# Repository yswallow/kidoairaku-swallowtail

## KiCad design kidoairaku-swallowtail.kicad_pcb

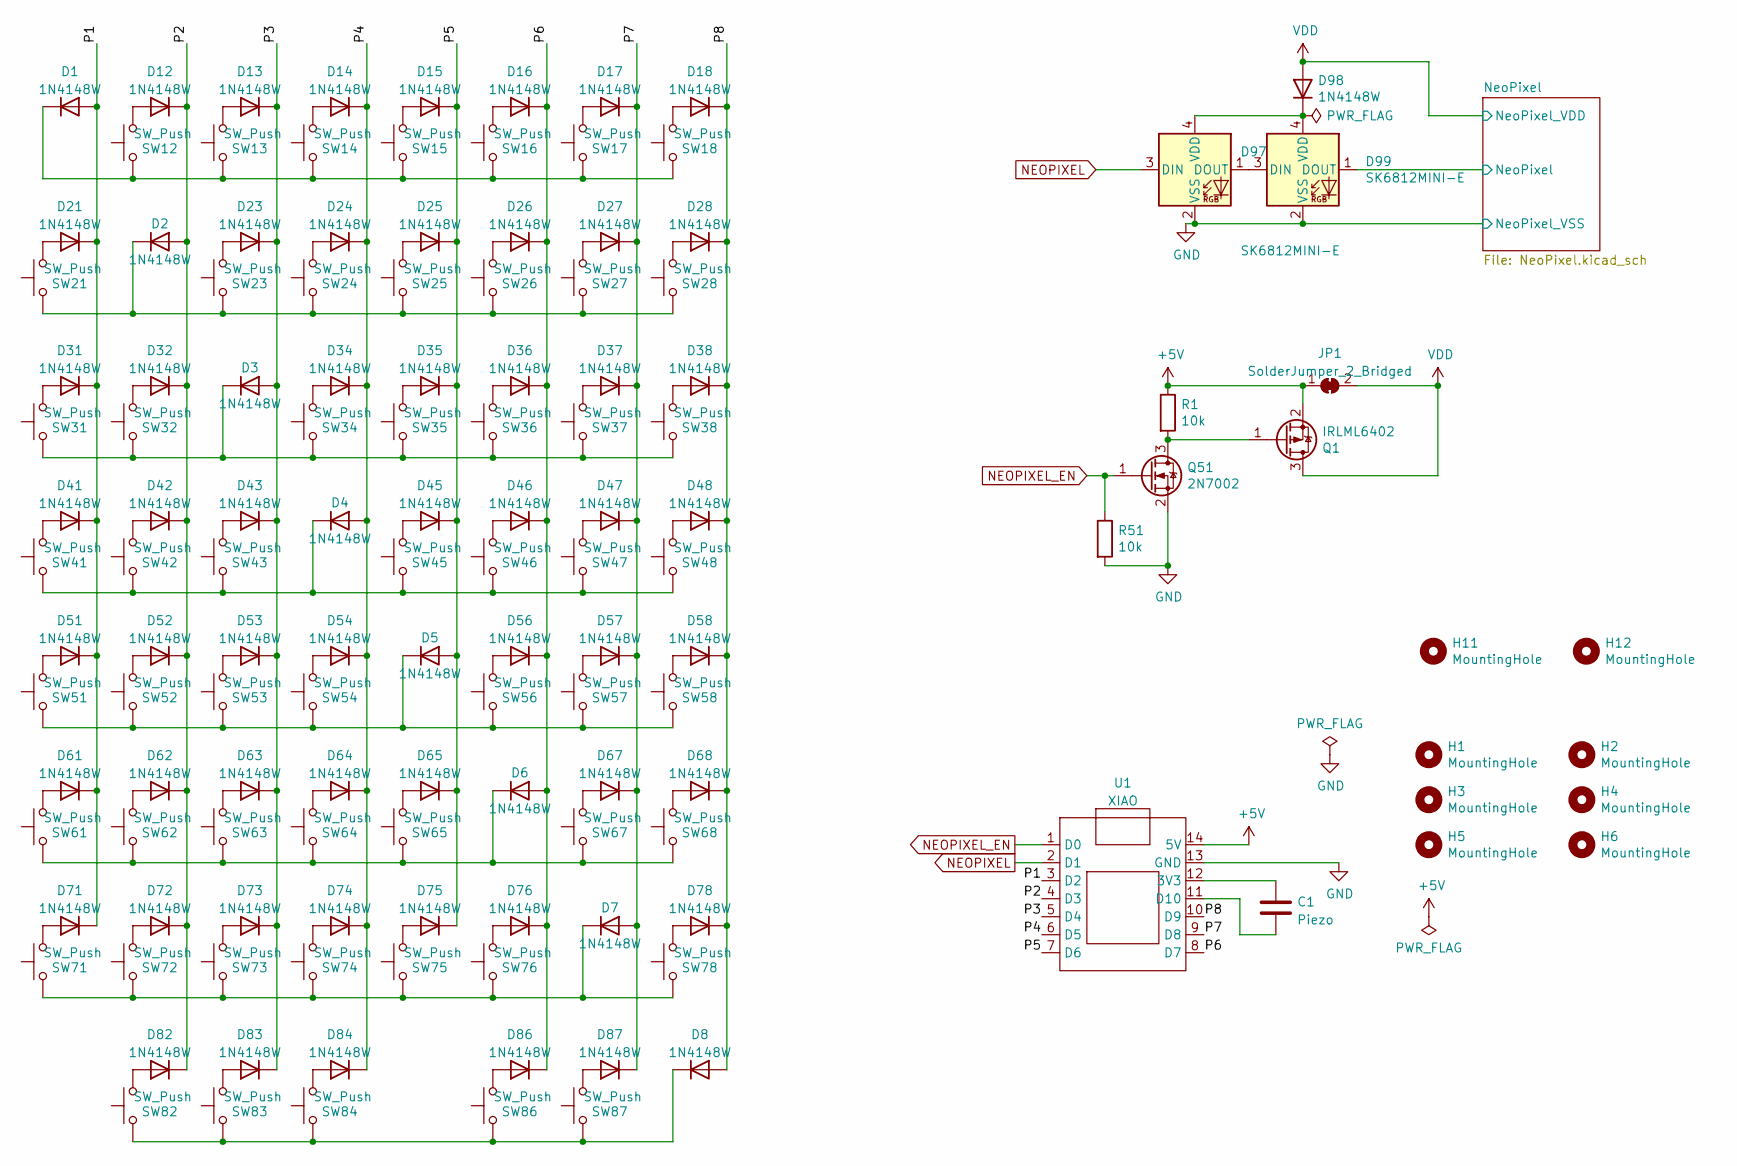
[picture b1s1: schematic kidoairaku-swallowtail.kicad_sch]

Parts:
C1: Piezo; C_Radial_D10.0mm_H12.5mm_P5.00mm
D1, D2, D3, D4, D5, D6, D7, D8, D12, D13, D14, D15, D16, D17, D18, D21, D23, D24, D25, D26, D27, D28, D31, D32, D34, D35, D36, D37, D38, D41, D42, D43, D45, D46, D47, D48, D51, D52, D53, D54, D56, D57, D58, D61, D62, D63, D64, D65, D67, D68, D71, D72, D73, D74, D75, D76, D78, D82, D83, D84, D86, D87, D98: 1N4148W; D_SOD-123
D97, D99: SK6812MINI-E; SK6812MINI-E_NoSilk-dril-PCBA
H1, H2, H3, H4, H5, H6, H11, H12: MountingHole; MountingHole_2.2mm_M2
JP1: SolderJumper_2_Bridged; SolderJumper-2_P1.3mm_Bridged_RoundedPad1.0x1.5mm
Q1: IRLML6402; SOT-23
Q51: 2N7002; SOT-23
R1, R51: 10k; R_1206_3216Metric_Pad1.30x1.75mm_HandSolder
SW12, SW13, SW14, SW15, SW16, SW17, SW18, SW21, SW23, SW24, SW25, SW26, SW27, SW28, SW31, SW32, SW34, SW35, SW36, SW37, SW38, SW41, SW42, SW43, SW45, SW46, SW47, SW48, SW51, SW52, SW53, SW54, SW56, SW57, SW58, SW61, SW62, SW63, SW64, SW65, SW67, SW68, SW71, SW72, SW73, SW74, SW75, SW76, SW78, SW82, SW83, SW84, SW86, SW87: SW_Push; SW_Choc_1U
U1: XIAO; Seeed XIAO SMD

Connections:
+5V: JP1.1 (A), Q1.2 (S), R1.1, U1.14 (5V)
/NeoPixel/NeoPixel: D99.1 (DOUT); also elsewhere on the board
/P1: D1.2 (A), D21.1 (K), D31.1 (K), D41.1 (K), D51.1 (K), D61.1 (K), D71.1 (K), U1.3 (D2)
/P2: D2.2 (A), D12.1 (K), D32.1 (K), D42.1 (K), D52.1 (K), D62.1 (K), D72.1 (K), D82.1 (K), U1.4 (D3)
/P3: D3.2 (A), D13.1 (K), D23.1 (K), D43.1 (K), D53.1 (K), D63.1 (K), D73.1 (K), D83.1 (K), U1.5 (D4)
/P4: D4.2 (A), D14.1 (K), D24.1 (K), D34.1 (K), D54.1 (K), D64.1 (K), D74.1 (K), D84.1 (K), U1.6 (D5)
/P5: D5.2 (A), D15.1 (K), D25.1 (K), D35.1 (K), D45.1 (K), D65.1 (K), D75.1 (K), U1.7 (D6)
/P6: D6.2 (A), D16.1 (K), D26.1 (K), D36.1 (K), D46.1 (K), D56.1 (K), D76.1 (K), D86.1 (K), U1.8 (D7)
/P7: D7.2 (A), D17.1 (K), D27.1 (K), D37.1 (K), D47.1 (K), D57.1 (K), D67.1 (K), D87.1 (K), U1.9 (D8)
/P8: D8.2 (A), D18.1 (K), D28.1 (K), D38.1 (K), D48.1 (K), D58.1 (K), D68.1 (K), D78.1 (K), U1.10 (D9)
GND: D97.2 (VSS), D99.2 (VSS), Q51.2 (S), R51.2, U1.13 (GND); also elsewhere on the board
NEOPIXEL: D97.3 (DIN), U1.2 (D1)
NEOPIXEL_EN: Q51.1 (G), R51.1, U1.1 (D0)
unnamed: D1.1 (K), SW12.2, SW13.2, SW14.2, SW15.2, SW16.2, SW17.2, SW18.2
unnamed: D2.1 (K), SW21.2, SW23.2, SW24.2, SW25.2, SW26.2, SW27.2, SW28.2
unnamed: D3.1 (K), SW31.2, SW32.2, SW34.2, SW35.2, SW36.2, SW37.2, SW38.2
unnamed: D4.1 (K), SW41.2, SW42.2, SW43.2, SW45.2, SW46.2, SW47.2, SW48.2
unnamed: D5.1 (K), SW51.2, SW52.2, SW53.2, SW54.2, SW56.2, SW57.2, SW58.2
unnamed: D6.1 (K), SW61.2, SW62.2, SW63.2, SW64.2, SW65.2, SW67.2, SW68.2
unnamed: D7.1 (K), SW71.2, SW72.2, SW73.2, SW74.2, SW75.2, SW76.2, SW78.2
unnamed: D8.1 (K), SW82.2, SW83.2, SW84.2, SW86.2, SW87.2
unnamed: D12.2 (A), SW12.1
unnamed: D13.2 (A), SW13.1
unnamed: D14.2 (A), SW14.1
unnamed: D15.2 (A), SW15.1
unnamed: D16.2 (A), SW16.1
unnamed: D17.2 (A), SW17.1
unnamed: D18.2 (A), SW18.1
unnamed: D21.2 (A), SW21.1
unnamed: D23.2 (A), SW23.1
unnamed: D24.2 (A), SW24.1
unnamed: D25.2 (A), SW25.1
unnamed: D26.2 (A), SW26.1
unnamed: D27.2 (A), SW27.1
unnamed: D28.2 (A), SW28.1
unnamed: D31.2 (A), SW31.1
unnamed: D32.2 (A), SW32.1
unnamed: D34.2 (A), SW34.1
unnamed: D35.2 (A), SW35.1
unnamed: D36.2 (A), SW36.1
unnamed: D37.2 (A), SW37.1
unnamed: D38.2 (A), SW38.1
unnamed: D41.2 (A), SW41.1
unnamed: D42.2 (A), SW42.1
unnamed: D43.2 (A), SW43.1
unnamed: D45.2 (A), SW45.1
unnamed: D46.2 (A), SW46.1
unnamed: D47.2 (A), SW47.1
unnamed: D48.2 (A), SW48.1
unnamed: D51.2 (A), SW51.1
unnamed: D52.2 (A), SW52.1
unnamed: D53.2 (A), SW53.1
unnamed: D54.2 (A), SW54.1
unnamed: D56.2 (A), SW56.1
unnamed: D57.2 (A), SW57.1
unnamed: D58.2 (A), SW58.1
unnamed: D61.2 (A), SW61.1
unnamed: D62.2 (A), SW62.1
unnamed: D63.2 (A), SW63.1
unnamed: D64.2 (A), SW64.1
unnamed: D65.2 (A), SW65.1
unnamed: D67.2 (A), SW67.1
unnamed: D68.2 (A), SW68.1
unnamed: D71.2 (A), SW71.1
unnamed: D72.2 (A), SW72.1
unnamed: D73.2 (A), SW73.1
unnamed: D74.2 (A), SW74.1
unnamed: D75.2 (A), SW75.1
unnamed: D76.2 (A), SW76.1
unnamed: D78.2 (A), SW78.1
unnamed: D82.2 (A), SW82.1
unnamed: D83.2 (A), SW83.1
unnamed: D84.2 (A), SW84.1
unnamed: D86.2 (A), SW86.1
unnamed: D87.2 (A), SW87.1
unnamed: D97.1 (DOUT), D99.3 (DIN)
unnamed: D97.4 (VDD), D98.1 (K), D99.4 (VDD)
unnamed: Q1.1 (G), Q51.3 (D), R1.2
unnamed: C1.2, U1.11 (D10)
unnamed: C1.1, U1.12 (3V3)
VDD: D98.2 (A), JP1.2 (B), Q1.3 (D); also elsewhere on the board

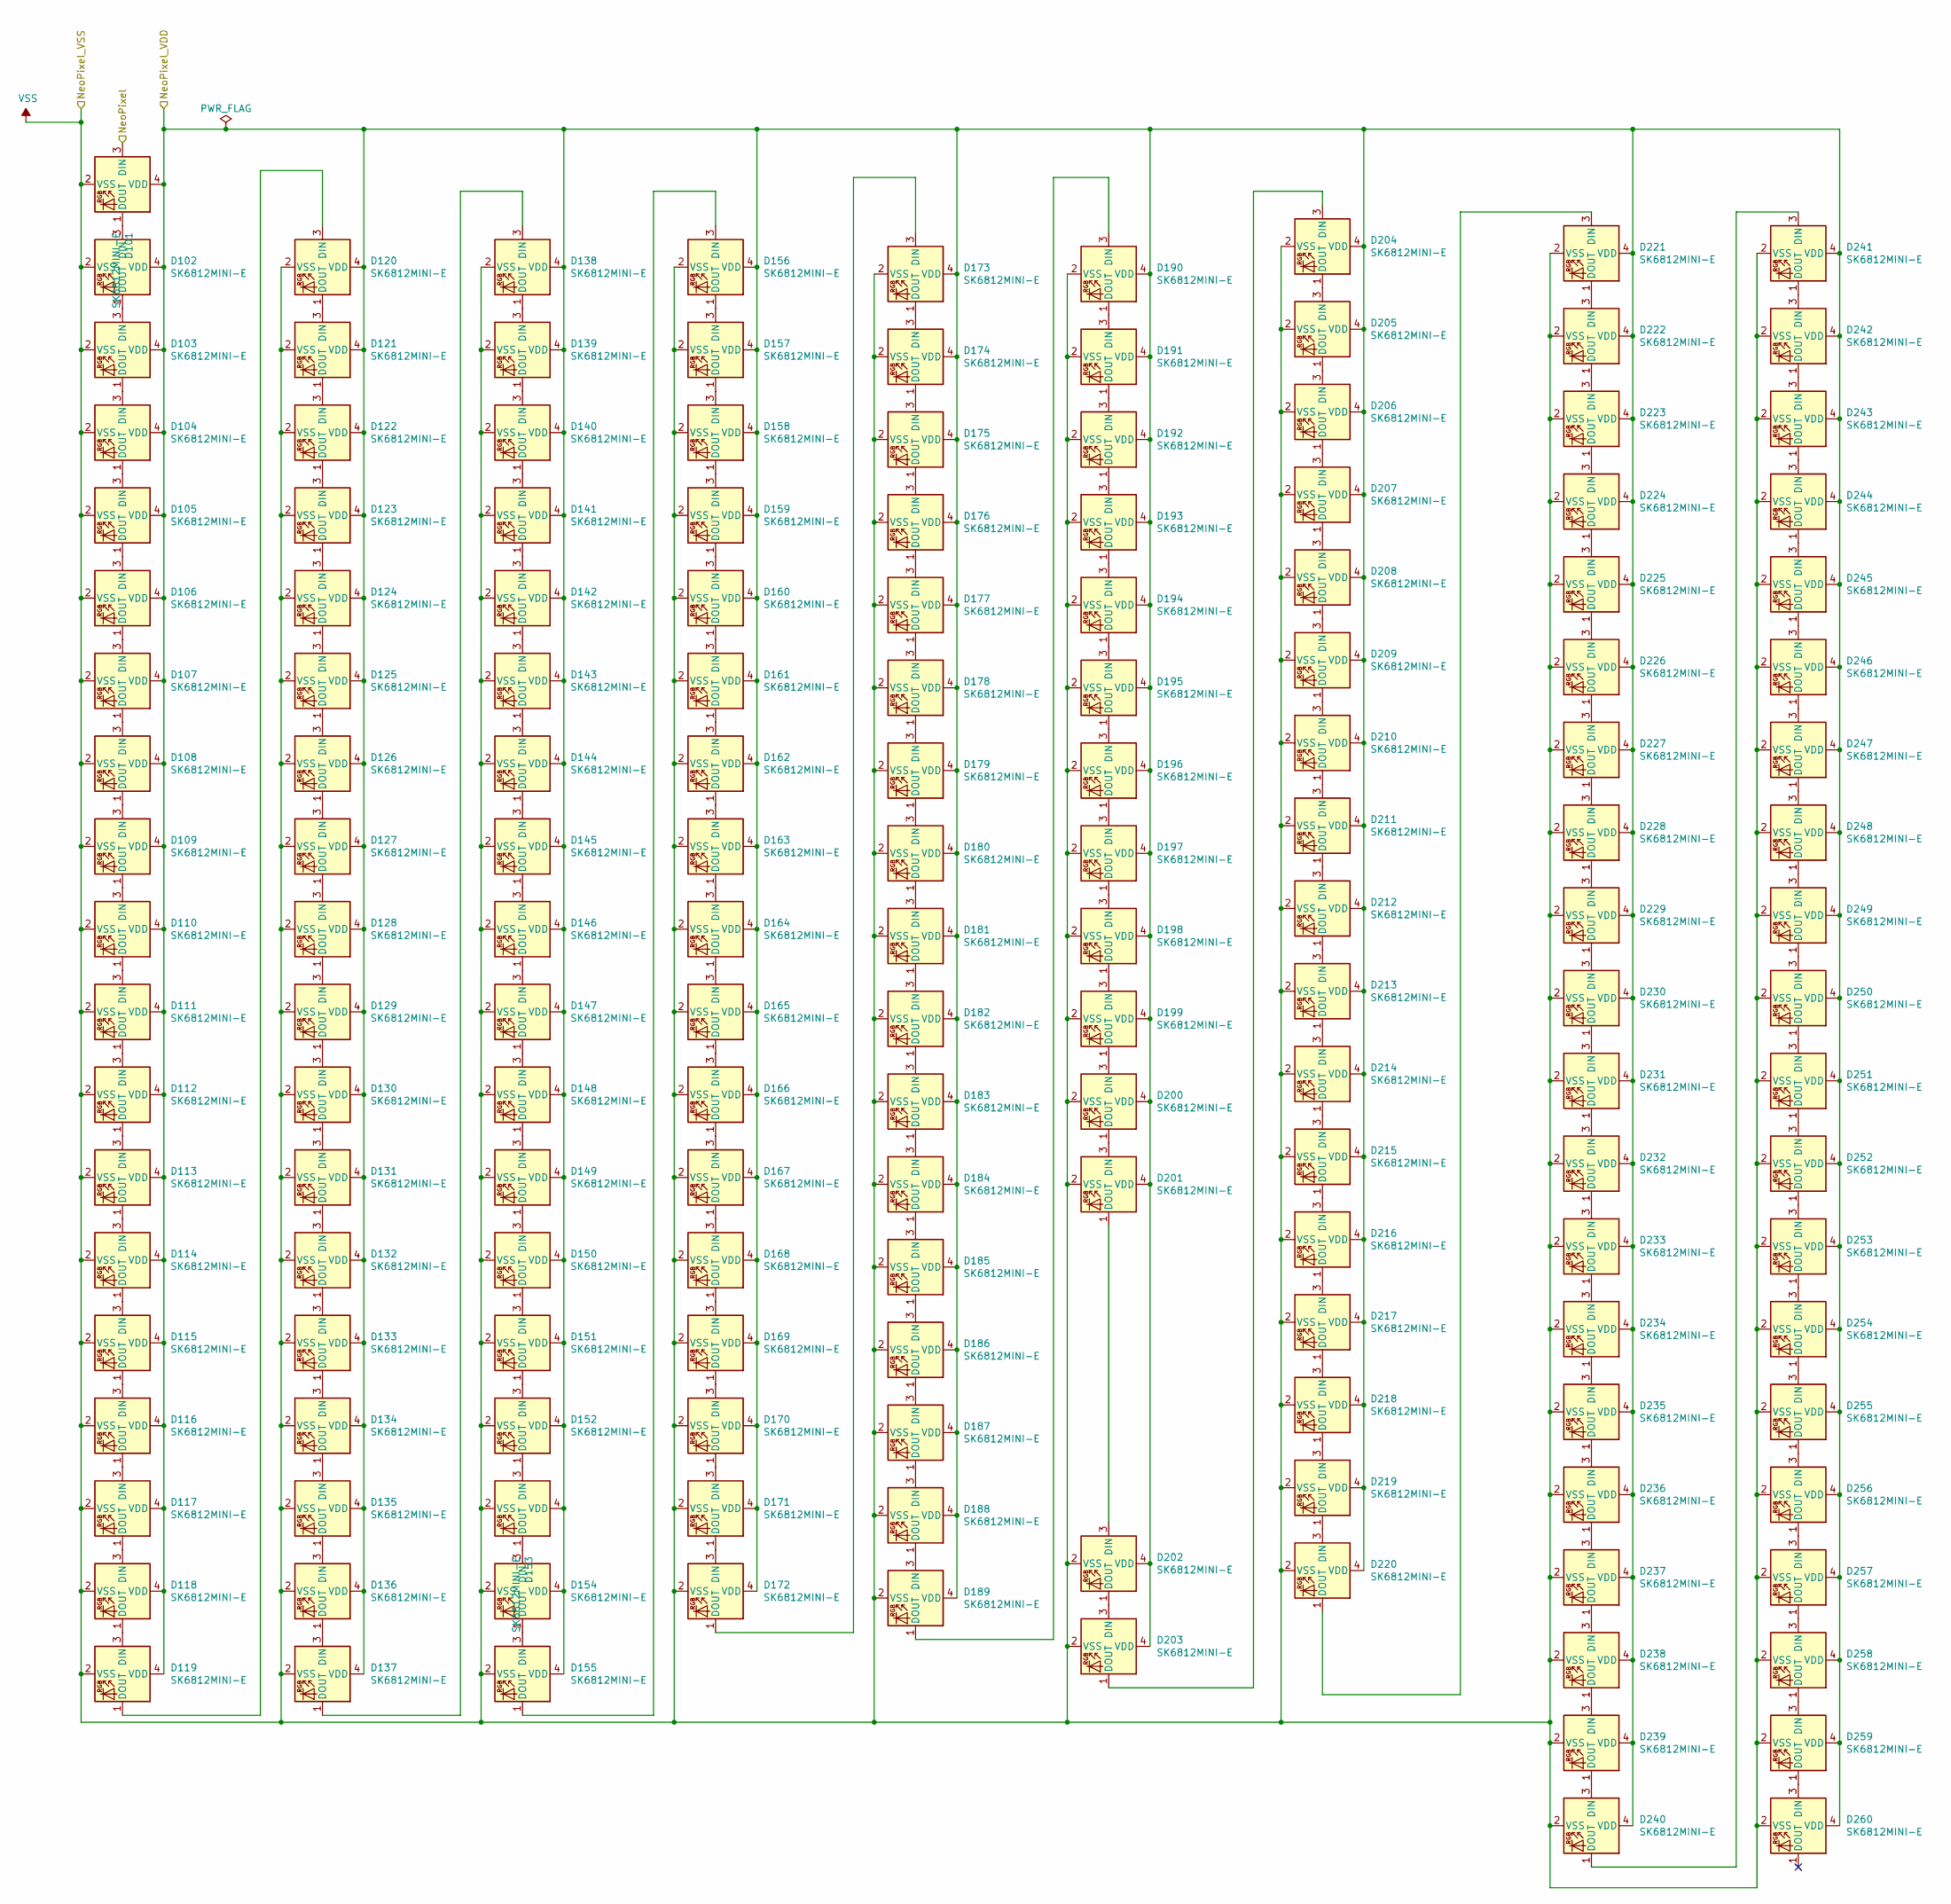
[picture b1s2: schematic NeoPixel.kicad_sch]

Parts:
D101, D102, D103, D104, D105, D106, D107, D108, D109, D110, D111, D112, D113, D114, D115, D116, D117, D118, D119, D120, D121, D122, D123, D124, D125, D126, D127, D128, D129, D130, D131, D132, D133, D134, D135, D136, D137, D138, D139, D140, D141, D142, D143, D144, D145, D146, D147, D148, D149, D150, D151, D152, D153, D154, D155, D156, D157, D158, D159, D160, D161, D162, D163, D164, D165, D166, D167, D168, D169, D170, D171, D172, D173, D174, D175, D176, D177, D178, D179, D180, D181, D182, D183, D184, D185, D186, D187, D188, D189, D190, D191, D192, D193, D194, D195, D196, D197, D198, D199, D200, D201, D202, D203, D204, D205, D206, D207, D208, D209, D210, D211, D212, D213, D214, D215, D216, D217, D218, D219, D220, D221, D222, D223, D224, D225, D226, D227, D228, D229, D230, D231, D232, D233, D234, D235, D236, D237, D238, D239, D240, D241, D242, D243, D244, D245, D246, D247, D248, D249, D250, D251, D252, D253, D254, D255, D256, D257, D258, D259, D260: SK6812MINI-E; SK6812MINI-E_NoSilk-dril-PCBA

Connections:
/NeoPixel/NeoPixel: D101.3 (DIN); also elsewhere on the board
GND: D101.2 (VSS), D102.2 (VSS), D103.2 (VSS), D104.2 (VSS), D105.2 (VSS), D106.2 (VSS), D107.2 (VSS), D108.2 (VSS), D109.2 (VSS), D110.2 (VSS), D111.2 (VSS), D112.2 (VSS), D113.2 (VSS), D114.2 (VSS), D115.2 (VSS), D116.2 (VSS), D117.2 (VSS), D118.2 (VSS), D119.2 (VSS), D120.2 (VSS), D121.2 (VSS), D122.2 (VSS), D123.2 (VSS), D124.2 (VSS), D125.2 (VSS), D126.2 (VSS), D127.2 (VSS), D128.2 (VSS), D129.2 (VSS), D130.2 (VSS), D131.2 (VSS), D132.2 (VSS), D133.2 (VSS), D134.2 (VSS), D135.2 (VSS), D136.2 (VSS), D137.2 (VSS), D138.2 (VSS), D139.2 (VSS), D140.2 (VSS), D141.2 (VSS), D142.2 (VSS), D143.2 (VSS), D144.2 (VSS), D145.2 (VSS), D146.2 (VSS), D147.2 (VSS), D148.2 (VSS), D149.2 (VSS), D150.2 (VSS), D151.2 (VSS), D152.2 (VSS), D153.2 (VSS), D154.2 (VSS), D155.2 (VSS), D156.2 (VSS), D157.2 (VSS), D158.2 (VSS), D159.2 (VSS), D160.2 (VSS), D161.2 (VSS), D162.2 (VSS), D163.2 (VSS), D164.2 (VSS), D165.2 (VSS), D166.2 (VSS), D167.2 (VSS), D168.2 (VSS), D169.2 (VSS), D170.2 (VSS), D171.2 (VSS), D172.2 (VSS), D173.2 (VSS), D174.2 (VSS), D175.2 (VSS), D176.2 (VSS), D177.2 (VSS), D178.2 (VSS), D179.2 (VSS), D180.2 (VSS), D181.2 (VSS), D182.2 (VSS), D183.2 (VSS), D184.2 (VSS), D185.2 (VSS), D186.2 (VSS), D187.2 (VSS), D188.2 (VSS), D189.2 (VSS), D190.2 (VSS), D191.2 (VSS), D192.2 (VSS), D193.2 (VSS), D194.2 (VSS), D195.2 (VSS), D196.2 (VSS), D197.2 (VSS), D198.2 (VSS), D199.2 (VSS), D200.2 (VSS), D201.2 (VSS), D202.2 (VSS), D203.2 (VSS), D204.2 (VSS), D205.2 (VSS), D206.2 (VSS), D207.2 (VSS), D208.2 (VSS), D209.2 (VSS), D210.2 (VSS), D211.2 (VSS), D212.2 (VSS), D213.2 (VSS), D214.2 (VSS), D215.2 (VSS), D216.2 (VSS), D217.2 (VSS), D218.2 (VSS), D219.2 (VSS), D220.2 (VSS), D221.2 (VSS), D222.2 (VSS), D223.2 (VSS), D224.2 (VSS), D225.2 (VSS), D226.2 (VSS), D227.2 (VSS), D228.2 (VSS), D229.2 (VSS), D230.2 (VSS), D231.2 (VSS), D232.2 (VSS), D233.2 (VSS), D234.2 (VSS), D235.2 (VSS), D236.2 (VSS), D237.2 (VSS), D238.2 (VSS), D239.2 (VSS), D240.2 (VSS), D241.2 (VSS), D242.2 (VSS), D243.2 (VSS), D244.2 (VSS), D245.2 (VSS), D246.2 (VSS), D247.2 (VSS), D248.2 (VSS), D249.2 (VSS), D250.2 (VSS), D251.2 (VSS), D252.2 (VSS), D253.2 (VSS), D254.2 (VSS), D255.2 (VSS), D256.2 (VSS), D257.2 (VSS), D258.2 (VSS), D259.2 (VSS), D260.2 (VSS); also elsewhere on the board
unnamed: D101.1 (DOUT), D102.3 (DIN)
unnamed: D102.1 (DOUT), D103.3 (DIN)
unnamed: D103.1 (DOUT), D104.3 (DIN)
unnamed: D104.1 (DOUT), D105.3 (DIN)
unnamed: D105.1 (DOUT), D106.3 (DIN)
unnamed: D106.1 (DOUT), D107.3 (DIN)
unnamed: D107.1 (DOUT), D108.3 (DIN)
unnamed: D108.1 (DOUT), D109.3 (DIN)
unnamed: D109.1 (DOUT), D110.3 (DIN)
unnamed: D110.1 (DOUT), D111.3 (DIN)
unnamed: D111.1 (DOUT), D112.3 (DIN)
unnamed: D112.1 (DOUT), D113.3 (DIN)
unnamed: D113.1 (DOUT), D114.3 (DIN)
unnamed: D114.1 (DOUT), D115.3 (DIN)
unnamed: D115.1 (DOUT), D116.3 (DIN)
unnamed: D116.1 (DOUT), D117.3 (DIN)
unnamed: D117.1 (DOUT), D118.3 (DIN)
unnamed: D118.1 (DOUT), D119.3 (DIN)
unnamed: D119.1 (DOUT), D120.3 (DIN)
unnamed: D120.1 (DOUT), D121.3 (DIN)
unnamed: D121.1 (DOUT), D122.3 (DIN)
unnamed: D122.1 (DOUT), D123.3 (DIN)
unnamed: D123.1 (DOUT), D124.3 (DIN)
unnamed: D124.1 (DOUT), D125.3 (DIN)
unnamed: D125.1 (DOUT), D126.3 (DIN)
unnamed: D126.1 (DOUT), D127.3 (DIN)
unnamed: D127.1 (DOUT), D128.3 (DIN)
unnamed: D128.1 (DOUT), D129.3 (DIN)
unnamed: D129.1 (DOUT), D130.3 (DIN)
unnamed: D130.1 (DOUT), D131.3 (DIN)
unnamed: D131.1 (DOUT), D132.3 (DIN)
unnamed: D132.1 (DOUT), D133.3 (DIN)
unnamed: D133.1 (DOUT), D134.3 (DIN)
unnamed: D134.1 (DOUT), D135.3 (DIN)
unnamed: D135.1 (DOUT), D136.3 (DIN)
unnamed: D136.1 (DOUT), D137.3 (DIN)
unnamed: D137.1 (DOUT), D138.3 (DIN)
unnamed: D138.1 (DOUT), D139.3 (DIN)
unnamed: D139.1 (DOUT), D140.3 (DIN)
unnamed: D140.1 (DOUT), D141.3 (DIN)
unnamed: D141.1 (DOUT), D142.3 (DIN)
unnamed: D142.1 (DOUT), D143.3 (DIN)
unnamed: D143.1 (DOUT), D144.3 (DIN)
unnamed: D144.1 (DOUT), D145.3 (DIN)
unnamed: D145.1 (DOUT), D146.3 (DIN)
unnamed: D146.1 (DOUT), D147.3 (DIN)
unnamed: D147.1 (DOUT), D148.3 (DIN)
unnamed: D148.1 (DOUT), D149.3 (DIN)
unnamed: D149.1 (DOUT), D150.3 (DIN)
unnamed: D150.1 (DOUT), D151.3 (DIN)
unnamed: D151.1 (DOUT), D152.3 (DIN)
unnamed: D152.1 (DOUT), D153.3 (DIN)
unnamed: D153.1 (DOUT), D154.3 (DIN)
unnamed: D154.1 (DOUT), D155.3 (DIN)
unnamed: D155.1 (DOUT), D156.3 (DIN)
unnamed: D156.1 (DOUT), D157.3 (DIN)
unnamed: D157.1 (DOUT), D158.3 (DIN)
unnamed: D158.1 (DOUT), D159.3 (DIN)
unnamed: D159.1 (DOUT), D160.3 (DIN)
unnamed: D160.1 (DOUT), D161.3 (DIN)
unnamed: D161.1 (DOUT), D162.3 (DIN)
unnamed: D162.1 (DOUT), D163.3 (DIN)
unnamed: D163.1 (DOUT), D164.3 (DIN)
unnamed: D164.1 (DOUT), D165.3 (DIN)
unnamed: D165.1 (DOUT), D166.3 (DIN)
unnamed: D166.1 (DOUT), D167.3 (DIN)
unnamed: D167.1 (DOUT), D168.3 (DIN)
unnamed: D168.1 (DOUT), D169.3 (DIN)
unnamed: D169.1 (DOUT), D170.3 (DIN)
unnamed: D170.1 (DOUT), D171.3 (DIN)
unnamed: D171.1 (DOUT), D172.3 (DIN)
unnamed: D172.1 (DOUT), D173.3 (DIN)
unnamed: D173.1 (DOUT), D174.3 (DIN)
unnamed: D174.1 (DOUT), D175.3 (DIN)
unnamed: D175.1 (DOUT), D176.3 (DIN)
unnamed: D176.1 (DOUT), D177.3 (DIN)
unnamed: D177.1 (DOUT), D178.3 (DIN)
unnamed: D178.1 (DOUT), D179.3 (DIN)
unnamed: D179.1 (DOUT), D180.3 (DIN)
unnamed: D180.1 (DOUT), D181.3 (DIN)
unnamed: D181.1 (DOUT), D182.3 (DIN)
unnamed: D182.1 (DOUT), D183.3 (DIN)
unnamed: D183.1 (DOUT), D184.3 (DIN)
unnamed: D184.1 (DOUT), D185.3 (DIN)
unnamed: D185.1 (DOUT), D186.3 (DIN)
unnamed: D186.1 (DOUT), D187.3 (DIN)
unnamed: D187.1 (DOUT), D188.3 (DIN)
unnamed: D188.1 (DOUT), D189.3 (DIN)
unnamed: D189.1 (DOUT), D190.3 (DIN)
unnamed: D190.1 (DOUT), D191.3 (DIN)
unnamed: D191.1 (DOUT), D192.3 (DIN)
unnamed: D192.1 (DOUT), D193.3 (DIN)
unnamed: D193.1 (DOUT), D194.3 (DIN)
unnamed: D194.1 (DOUT), D195.3 (DIN)
unnamed: D195.1 (DOUT), D196.3 (DIN)
unnamed: D196.1 (DOUT), D197.3 (DIN)
unnamed: D197.1 (DOUT), D198.3 (DIN)
unnamed: D198.1 (DOUT), D199.3 (DIN)
unnamed: D199.1 (DOUT), D200.3 (DIN)
unnamed: D200.1 (DOUT), D201.3 (DIN)
unnamed: D201.1 (DOUT), D202.3 (DIN)
unnamed: D202.1 (DOUT), D203.3 (DIN)
unnamed: D203.1 (DOUT), D204.3 (DIN)
unnamed: D204.1 (DOUT), D205.3 (DIN)
unnamed: D205.1 (DOUT), D206.3 (DIN)
unnamed: D206.1 (DOUT), D207.3 (DIN)
unnamed: D207.1 (DOUT), D208.3 (DIN)
unnamed: D208.1 (DOUT), D209.3 (DIN)
unnamed: D209.1 (DOUT), D210.3 (DIN)
unnamed: D210.1 (DOUT), D211.3 (DIN)
unnamed: D211.1 (DOUT), D212.3 (DIN)
unnamed: D212.1 (DOUT), D213.3 (DIN)
unnamed: D213.1 (DOUT), D214.3 (DIN)
unnamed: D214.1 (DOUT), D215.3 (DIN)
unnamed: D215.1 (DOUT), D216.3 (DIN)
unnamed: D216.1 (DOUT), D217.3 (DIN)
unnamed: D217.1 (DOUT), D218.3 (DIN)
unnamed: D218.1 (DOUT), D219.3 (DIN)
unnamed: D219.1 (DOUT), D220.3 (DIN)
unnamed: D220.1 (DOUT), D221.3 (DIN)
unnamed: D221.1 (DOUT), D222.3 (DIN)
unnamed: D222.1 (DOUT), D223.3 (DIN)
unnamed: D223.1 (DOUT), D224.3 (DIN)
unnamed: D224.1 (DOUT), D225.3 (DIN)
unnamed: D225.1 (DOUT), D226.3 (DIN)
unnamed: D226.1 (DOUT), D227.3 (DIN)
unnamed: D227.1 (DOUT), D228.3 (DIN)
unnamed: D228.1 (DOUT), D229.3 (DIN)
unnamed: D229.1 (DOUT), D230.3 (DIN)
unnamed: D230.1 (DOUT), D231.3 (DIN)
unnamed: D231.1 (DOUT), D232.3 (DIN)
unnamed: D232.1 (DOUT), D233.3 (DIN)
unnamed: D233.1 (DOUT), D234.3 (DIN)
unnamed: D234.1 (DOUT), D235.3 (DIN)
unnamed: D235.1 (DOUT), D236.3 (DIN)
unnamed: D236.1 (DOUT), D237.3 (DIN)
unnamed: D237.1 (DOUT), D238.3 (DIN)
unnamed: D238.1 (DOUT), D239.3 (DIN)
unnamed: D239.1 (DOUT), D240.3 (DIN)
unnamed: D240.1 (DOUT), D241.3 (DIN)
unnamed: D241.1 (DOUT), D242.3 (DIN)
unnamed: D242.1 (DOUT), D243.3 (DIN)
unnamed: D243.1 (DOUT), D244.3 (DIN)
unnamed: D244.1 (DOUT), D245.3 (DIN)
unnamed: D245.1 (DOUT), D246.3 (DIN)
unnamed: D246.1 (DOUT), D247.3 (DIN)
unnamed: D247.1 (DOUT), D248.3 (DIN)
unnamed: D248.1 (DOUT), D249.3 (DIN)
unnamed: D249.1 (DOUT), D250.3 (DIN)
unnamed: D250.1 (DOUT), D251.3 (DIN)
unnamed: D251.1 (DOUT), D252.3 (DIN)
unnamed: D252.1 (DOUT), D253.3 (DIN)
unnamed: D253.1 (DOUT), D254.3 (DIN)
unnamed: D254.1 (DOUT), D255.3 (DIN)
unnamed: D255.1 (DOUT), D256.3 (DIN)
unnamed: D256.1 (DOUT), D257.3 (DIN)
unnamed: D257.1 (DOUT), D258.3 (DIN)
unnamed: D258.1 (DOUT), D259.3 (DIN)
unnamed: D259.1 (DOUT), D260.3 (DIN)
VDD: D101.4 (VDD), D102.4 (VDD), D103.4 (VDD), D104.4 (VDD), D105.4 (VDD), D106.4 (VDD), D107.4 (VDD), D108.4 (VDD), D109.4 (VDD), D110.4 (VDD), D111.4 (VDD), D112.4 (VDD), D113.4 (VDD), D114.4 (VDD), D115.4 (VDD), D116.4 (VDD), D117.4 (VDD), D118.4 (VDD), D119.4 (VDD), D120.4 (VDD), D121.4 (VDD), D122.4 (VDD), D123.4 (VDD), D124.4 (VDD), D125.4 (VDD), D126.4 (VDD), D127.4 (VDD), D128.4 (VDD), D129.4 (VDD), D130.4 (VDD), D131.4 (VDD), D132.4 (VDD), D133.4 (VDD), D134.4 (VDD), D135.4 (VDD), D136.4 (VDD), D137.4 (VDD), D138.4 (VDD), D139.4 (VDD), D140.4 (VDD), D141.4 (VDD), D142.4 (VDD), D143.4 (VDD), D144.4 (VDD), D145.4 (VDD), D146.4 (VDD), D147.4 (VDD), D148.4 (VDD), D149.4 (VDD), D150.4 (VDD), D151.4 (VDD), D152.4 (VDD), D153.4 (VDD), D154.4 (VDD), D155.4 (VDD), D156.4 (VDD), D157.4 (VDD), D158.4 (VDD), D159.4 (VDD), D160.4 (VDD), D161.4 (VDD), D162.4 (VDD), D163.4 (VDD), D164.4 (VDD), D165.4 (VDD), D166.4 (VDD), D167.4 (VDD), D168.4 (VDD), D169.4 (VDD), D170.4 (VDD), D171.4 (VDD), D172.4 (VDD), D173.4 (VDD), D174.4 (VDD), D175.4 (VDD), D176.4 (VDD), D177.4 (VDD), D178.4 (VDD), D179.4 (VDD), D180.4 (VDD), D181.4 (VDD), D182.4 (VDD), D183.4 (VDD), D184.4 (VDD), D185.4 (VDD), D186.4 (VDD), D187.4 (VDD), D188.4 (VDD), D189.4 (VDD), D190.4 (VDD), D191.4 (VDD), D192.4 (VDD), D193.4 (VDD), D194.4 (VDD), D195.4 (VDD), D196.4 (VDD), D197.4 (VDD), D198.4 (VDD), D199.4 (VDD), D200.4 (VDD), D201.4 (VDD), D202.4 (VDD), D203.4 (VDD), D204.4 (VDD), D205.4 (VDD), D206.4 (VDD), D207.4 (VDD), D208.4 (VDD), D209.4 (VDD), D210.4 (VDD), D211.4 (VDD), D212.4 (VDD), D213.4 (VDD), D214.4 (VDD), D215.4 (VDD), D216.4 (VDD), D217.4 (VDD), D218.4 (VDD), D219.4 (VDD), D220.4 (VDD), D221.4 (VDD), D222.4 (VDD), D223.4 (VDD), D224.4 (VDD), D225.4 (VDD), D226.4 (VDD), D227.4 (VDD), D228.4 (VDD), D229.4 (VDD), D230.4 (VDD), D231.4 (VDD), D232.4 (VDD), D233.4 (VDD), D234.4 (VDD), D235.4 (VDD), D236.4 (VDD), D237.4 (VDD), D238.4 (VDD), D239.4 (VDD), D240.4 (VDD), D241.4 (VDD), D242.4 (VDD), D243.4 (VDD), D244.4 (VDD), D245.4 (VDD), D246.4 (VDD), D247.4 (VDD), D248.4 (VDD), D249.4 (VDD), D250.4 (VDD), D251.4 (VDD), D252.4 (VDD), D253.4 (VDD), D254.4 (VDD), D255.4 (VDD), D256.4 (VDD), D257.4 (VDD), D258.4 (VDD), D259.4 (VDD), D260.4 (VDD); also elsewhere on the board

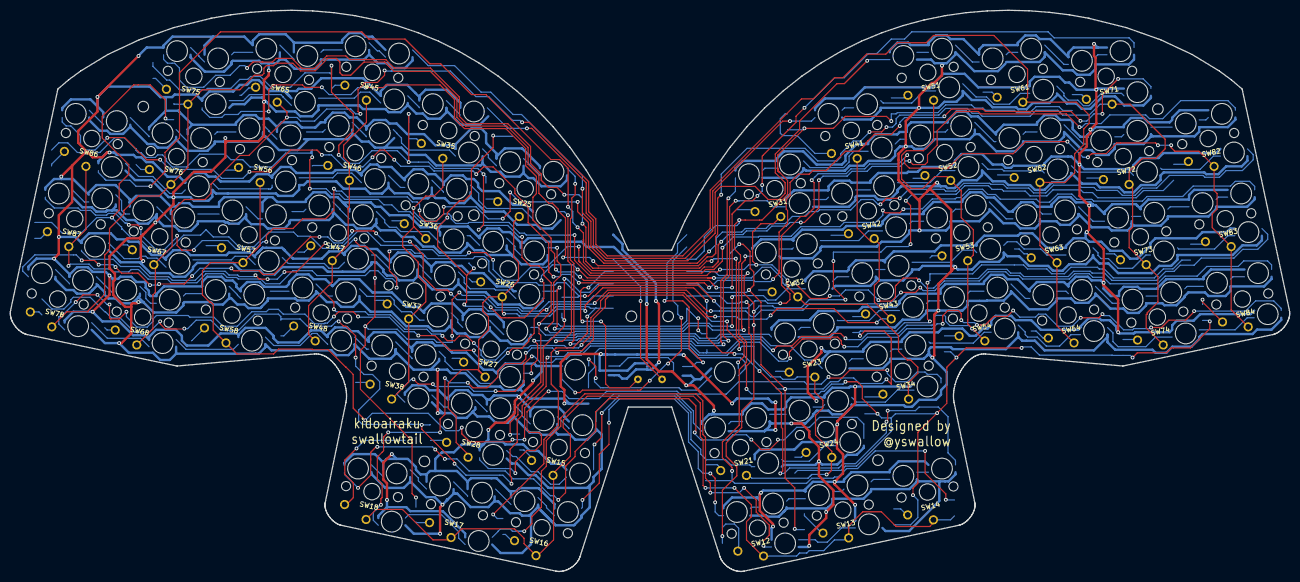
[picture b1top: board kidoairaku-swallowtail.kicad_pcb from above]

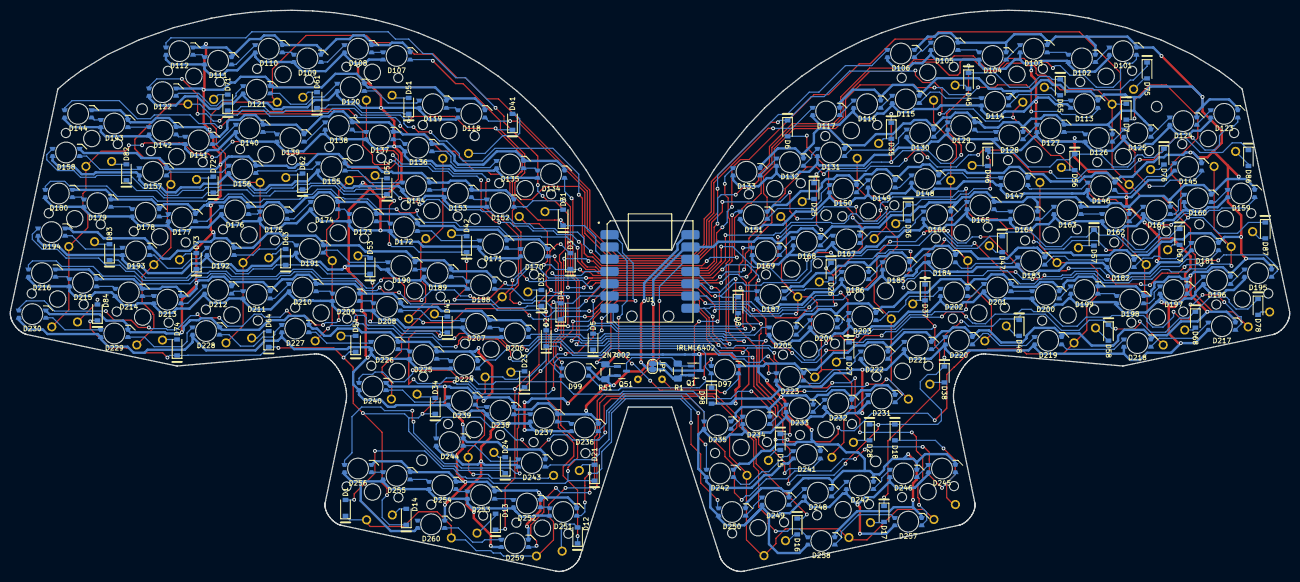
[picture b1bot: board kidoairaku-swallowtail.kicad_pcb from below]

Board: 2 copper layers, 265.1 x 116.3 mm, 294 parts (231 on the bottom side), 240 nets.

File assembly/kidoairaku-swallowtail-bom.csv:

Designator,MPN,Qty,Link,
"D193,D206,D148,D155,D102,D251,D207,D188,D137,D149,D229,D104,D197,D196,D150,D153,D175,D120,D165,D240,D258,D228,D221,D220,D135,D145, D257,D158,D186,D112,D224,D237,D248,D231,D154,D164,D129,D210,D130,D254,D167,D126,D177,D195,D117,D199,D185,D255,D203,D171,D191,D121,D178, D162,D260,D140,D151,D204,D122,D134,D113,D249,D156,D245,D239,D230,D172,D179,D108,D173,D128,D253,D211,D132,D250,D190,D252,D198,D143,D213, D232,D222,D99,D139,D142,D182,D205,D114,D174,D136,D223,D159,D181,D168,D200,D227,D116,D110,D189,D244,D105,D187,D236,D226,D217,D209,D138, D111,D202,D163,D144,D214,D234,D157,D242,D233,D109,D212,D184,D166,D152,D256,D238,D146,D161,D247,D147,D180,D194,D103,D125,D192,D201,D118, D123,D119,D259,D219,D127,D243,D246,D160,D218,D183,D169,D133,D170,D215,D235,D176,D225,D106,D131,D97,D107,D241,D141,D124,D101,D115,D208, D216","SK6803MINI-E",162,"https://www.aliexpress.com/item/1005003636607308.html",
"D21,D71,D37,D24,D63,D83,D17,D68,D34,D6,D46,D48,D41,D14,D13,D5,D57,D72,D86,D18,D75,D78,D98,D73,D87,D74,D54,D51,D62,D65,D58,D31,D4,D61, D53,D67,D3,D12,D76,D42,D28,D47,D64,D36,D2,D45,D84,D82,D32,D35,D7,D23,D38,D52,D26,D25,D16,D56,D15,D43,D8,D1,D27","1N4148W",63,,
"U1","Seeed Studio XIAO RP2040",1,"102010428",

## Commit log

2023-01-27 init
